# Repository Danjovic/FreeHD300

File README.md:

# FreeHD300
Emulador de HD para CP300

Baseado no projeto FreeHD [1] de F. Vecoven e na adaptação para o CP300 de Fábio Belavenuto [2]

Projetado para ser acomodado numa caixa plástica PB-207 da Patola [3]

[1] http://www.vecoven.com/trs80/trs80.html

[2] https://datassette.org/tech/tandy-trs-80/adaptador-do-cp-300-para-frehd

[3] http://www.patola.com.br/index.php?route=product/product&product_id=129

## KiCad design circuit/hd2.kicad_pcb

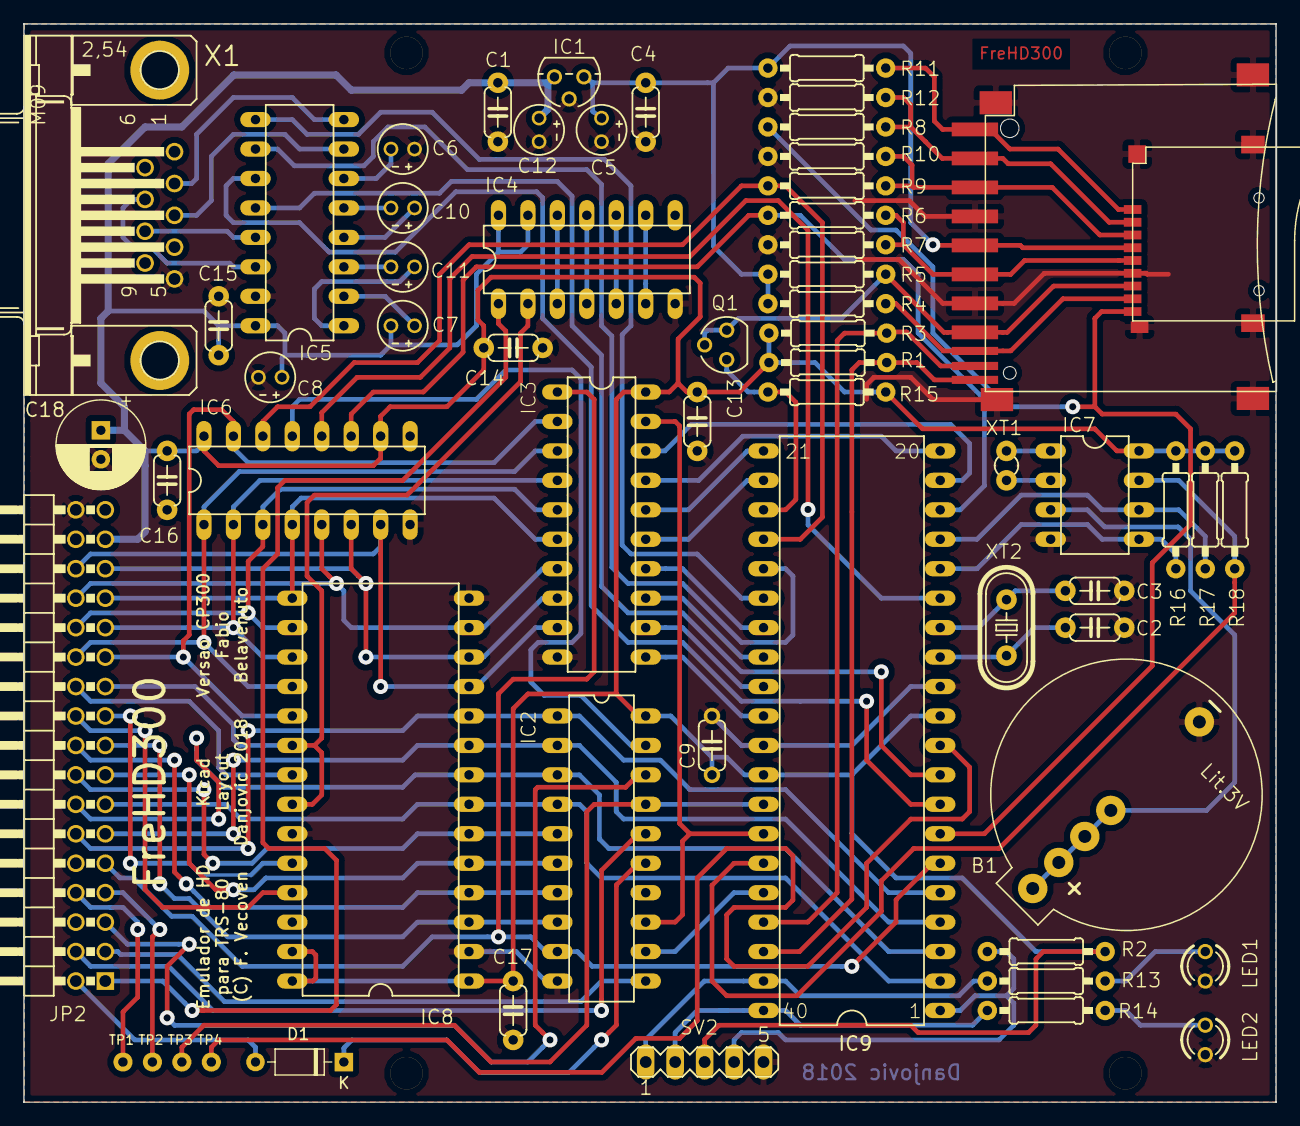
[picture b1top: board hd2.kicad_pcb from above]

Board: 2 copper layers, 108.0 x 93.0 mm, 61 parts (0 on the bottom side), 89 nets.

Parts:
B1: CR2032H
C1, C4, C9, C13, C14, C15, C16, C17: 100n; C050-024X044
C2, C3: 22p; C050-024X044
C5, C12: 10u; E2-4
C6, C7, C8, C10, C11: 1u; E2-4
C18: 220u; CP_Radial_D7.5mm_P2.50mm
D1: 1N4148; D_DO-35_SOD27_P7.62mm_Horizontal
IC1: LP2950-3V3; TO92
IC2: GAL16V8; DIL20
IC3: 74HCT245N; DIL20
IC4: 7404N; DIL14
IC5: MAX232; DIL16
IC6: 74HC595; DIL16
IC7: DS1307; DIL08
IC8: 2764; DIL28
IC9: PIC18F4620; PDIP-40
J1: MICROSD-9P; 9P-SMD-W_-RING
J2: SDMMC06132; 06132
JP2: PINHD-2X17_90; 2X17_90
LED1: VM; LED3MM
LED2: VD; LED3MM
Q1: BS170; SOT54E
R1, R3, R16, R17, R18: 4K7; 0207_10
R2, R4, R5, R12, R15: 10K; 0207_10
R6, R8, R11, R13, R14: 330; 0207_10
R7, R9, R10: 220; 0207_10
SV2: ICSP; MA05-1
TP1, TP2, TP3, TP4: PTR1PAD1-10; P1-10
X1: M09?SHP; M09HP
XT1: 32.768KHz; TC26V
XT2: 10MHz; HC49U-V

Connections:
+3V3: C4.1, C5.+, IC1.1, J1.4, J2.4, R4.2, R5.2, R12.2
+5V: C1.1, C7.-, C8.+, C9.1, C12.+, C13.1, C14.1, C15.1, C16.1, C17.1, C18.+, IC1.3, IC2.20, IC3.20, IC4.13, IC4.14, IC5.16, IC6.10, IC6.16, IC7.8, IC8.1, IC8.27, IC8.28, IC9.11, IC9.32, JP2.31, R1.2, R2.2, R3.2, R15.2, R16.2, R17.2, R18.2, SV2.3
/hd2_1/A4: IC2.5, IC8.6, JP2.16
/hd2_1/A5: IC2.6, IC8.5, JP2.15
/hd2_1/A6: IC2.7, IC8.4, JP2.18
/hd2_1/A7: IC2.8, IC8.3, JP2.17
/hd2_1/A8: IC8.25, JP2.20
/hd2_1/A9: IC8.24, JP2.19
/hd2_1/A10: IC8.21, JP2.22
/hd2_1/CS: J1.2, J2.1, R10.1, R11.2
/hd2_1/D0: IC3.2, IC6.15, IC8.19, JP2.23
/hd2_1/D1: IC3.3, IC6.1, IC8.18, JP2.24
/hd2_1/D2: IC3.4, IC6.2, IC8.17, JP2.25
/hd2_1/D3: IC3.5, IC6.3, IC8.16, JP2.26
/hd2_1/D4: IC3.6, IC6.4, IC8.15, JP2.27
/hd2_1/D5: IC3.7, IC6.5, IC8.13, JP2.28
/hd2_1/D6: IC3.8, IC6.6, IC8.12, JP2.29
/hd2_1/D7: IC3.9, IC6.7, IC8.11, JP2.30
/hd2_1/DAT1: J1.8, J2.8, R4.1
/hd2_1/DAT2: J1.1, J2.9, R12.1
/hd2_1/MISO: J1.7, J2.7, Q1.G, Q1.S, R5.1
/hd2_1/MOSI: J1.3, J2.2, R8.2, R9.1
/hd2_1/ROMD_CS: IC4.1, JP2.1
/hd2_1/SCLK: J1.5, J2.5, R6.2, R7.1
/hd2_1/_CTS: IC5.13, X1.8
/hd2_1/_RTS: IC5.14, X1.7
/hd2_1/_RX: IC5.8, X1.2
/hd2_1/_TX: IC5.7, X1.3
/hd2_1/~BUSINT: IC2.16, JP2.4
/hd2_1/~BUSWAIT: D1.1, IC2.15
/hd2_1/~DES_ROMD: IC4.2, IC8.20, IC8.22, JP2.21
/hd2_1/~IORQ: IC2.11, JP2.3
/hd2_1/~M1: JP2.8, TP1.TP
/hd2_1/~RESET: JP2.7, TP3.TP
/hd2_1/~STAT_OE: IC2.19, IC6.13
/hd2_1/~WR: IC2.18, JP2.5
/hd2_2/MCLR: IC9.1, R2.1, SV2.4
A0: IC2.1, IC8.10, IC9.5, JP2.12
A1: IC2.2, IC8.9, IC9.4, JP2.11
A2: IC2.3, IC8.8, IC9.3, JP2.14
A3: IC2.4, IC8.7, IC9.2, JP2.13
CTS: IC5.12, IC9.9
DD0: IC3.18, IC9.19
DD1: IC3.17, IC9.20
DD2: IC3.16, IC9.21
DD3: IC3.15, IC9.22
DD4: IC3.14, IC9.27
DD5: IC3.13, IC9.28
DD6: IC3.12, IC9.29
DD7: IC3.11, IC9.30
GND: B1.-, C1.2, C2.1, C3.1, C4.2, C5.-, C6.+, C8.-, C9.2, C12.-, C13.2, C14.2, C15.2, C16.2, C17.2, C18.-, IC1.2, IC2.10, IC3.10, IC4.7, IC5.15, IC6.8, IC7.4, IC8.2, IC8.14, IC8.23, IC9.12, IC9.31, J1.6, J1.COM, J1.SHL@1, J1.SHL@2, J1.SHL@3, J2.3, J2.6, J2.COM, J2.SHL@1, J2.SHL@2, J2.SHL@3, JP2.34, LED1.K, LED2.K, R6.1, R8.1, R11.1, SV2.5, X1.5
LED0: IC9.40, R14.2, SV2.2
LED1: IC9.39, R13.2, SV2.1
unnamed: B1.+@1, B1.+@2, B1.+@3, B1.+@4, IC7.3
unnamed: C2.2, IC9.13, XT2.1
unnamed: C3.2, IC9.14, XT2.2
unnamed: C6.-, IC5.6
unnamed: C7.+, IC5.2
unnamed: C10.+, IC5.4
unnamed: C10.-, IC5.5
unnamed: C11.+, IC5.1
unnamed: C11.-, IC5.3
unnamed: D1.2, JP2.2
unnamed: IC4.6, IC4.9
unnamed: IC4.5, IC4.10
unnamed: IC4.4, IC4.11
unnamed: IC4.3, IC4.12
unnamed: IC7.1, XT1.1
unnamed: IC7.2, XT1.2
unnamed: LED1.A, R13.1
unnamed: LED2.A, R14.1
RTC: IC7.7, IC9.35, R18.1
RTS: IC5.11, IC9.8
RX: IC5.9, IC9.26
SCL: IC7.6, IC9.17, R17.1
SDA: IC7.5, IC9.16, R16.1
SD_CD: IC9.37, J2.CD, R3.1
SD_CS: IC9.7, J1.CD, R10.2
SD_WRPROT: IC9.38, J2.WP, R1.1
SPARE1: IC2.17, IC9.33, TP2.TP
SPARE2: IC9.10, TP4.TP
SPI_CLK: IC6.11, IC9.18, R7.2
SPI_SDI: IC9.23, Q1.D, R15.1
SPI_SDO: IC6.14, IC9.24, R9.2
STAT_CS: IC6.12, IC9.15
TX: IC5.10, IC9.25
~PICSEL: IC2.13, IC3.19, IC9.34
~PICWAIT: IC2.12, IC9.36
~RD: IC2.9, IC3.1, IC9.6, JP2.9

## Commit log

2018-11-23 Adicionados capacitores de desacoplamento nos CIs
2018-11-28 Correcao na posicao dos nomes dos components no silk
2018-11-28 Adicionado Eletrolitico na entrada de alimentação
